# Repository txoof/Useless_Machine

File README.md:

# Useless Machine

## *Absolutely Useless, Completely Necessary*

This useless machine comes with everything you need to laser cut and assemble a box and add hardware of your choice. Both designs physically disconnect the batteries when not in use to provide months and months of useless uselessness!

It even comes in two flavors:
## [ItsyBitsy Version](ItsyBitsy_Version/ItsyBitsy_README.md)

The ItsyBitsy version is sassy, slightly passive aggressive, has lights, is programmable and hackable! It runs on AdaFruit's Circuit Python and code is well documented and easily modified with options for adding additional attack/retreat modes.

There's even a PCB schematic you can spin out from OSH Park or one of the other fab houses.
## [555 Timer Version ](555_Version/555_README.md)

This version is a fun way to explore PWM and 555 timers. The venerable 555 is a great tool for making das blinken lights, but also for driving pulse-width-modulated hardware like servos.

The 555 Version requires just a few parts and can be fabricated at home with protoboard or etching your own circuit. There are resist masks, drill instructions, a BOM and everything you need to build a your own 555 Useless Machine.

## [The Box](./enclosure/Enclosure_README.md)

Fire up the pew-pew laser and make yourself a box! Everything you need to create your own laser-cut box is here including DXF, SVG, artwork and OpenSCAD files. The DXF and SVG versions are set up for 4mm birch ply. If you intend to use something thicker or thinner, make sure you generate a new layout using the OpenSCAD files.

The OpenSCAD version is customizable takes advantage of the OpenSCAD customizer interface. M

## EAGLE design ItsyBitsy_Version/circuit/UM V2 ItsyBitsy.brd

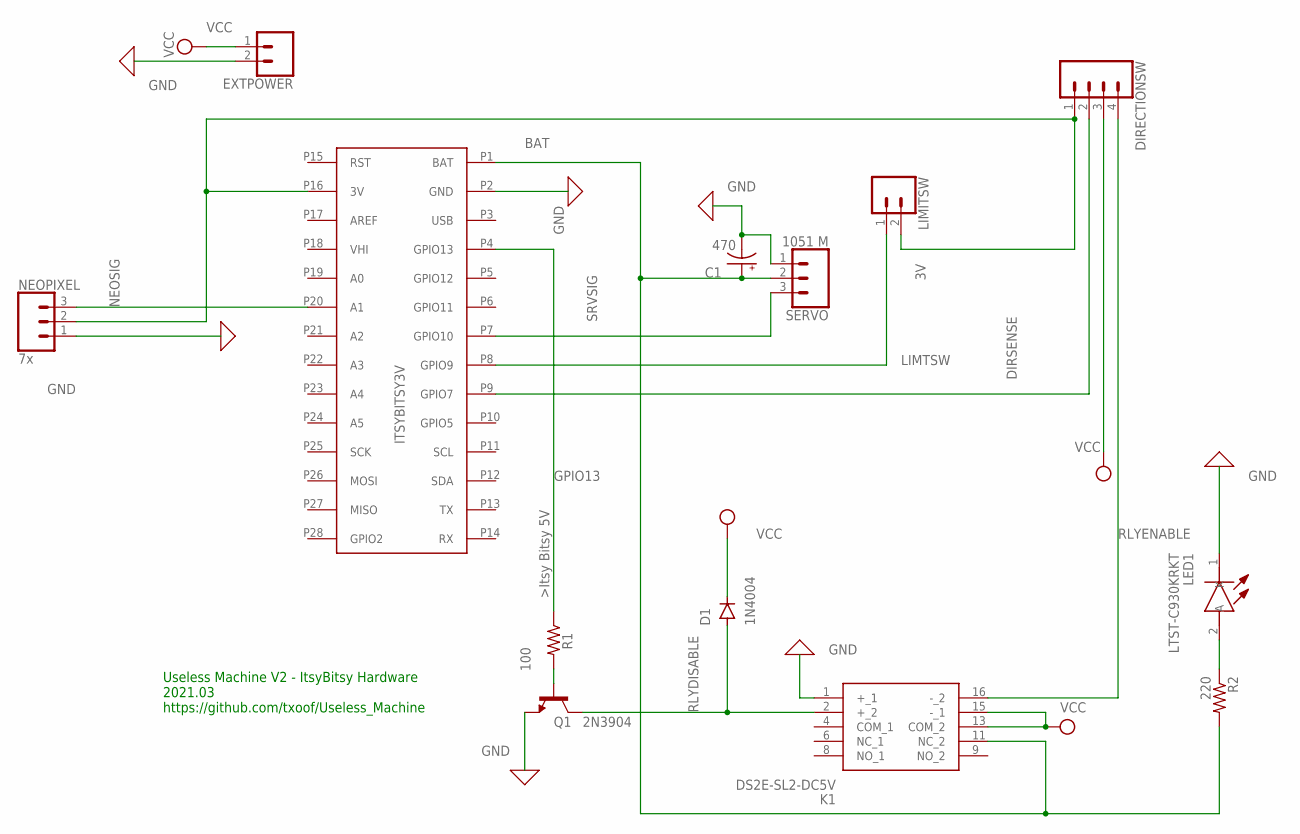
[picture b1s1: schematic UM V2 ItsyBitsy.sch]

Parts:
C1: 470; E2,5-6E
D1: 1N4004; DO41-10
DIRECTIONSW: Direction Sw; MOLEX-1X4
EXTPOWER: Limit Sw; MOLEX-1X2
K1: DS2E-SL2-DC5V; DS2ESL2DC5V
LED1: LTST-C930KRKT; LTSTC930KRKT
LIMITSW: Limit Sw; MOLEX-1X2
NEOPIXEL: 7x; MOLEX-1X3
Q1: 2N3904; TO92-CBE
R1: 100; M1206
R2: 220; M1206
SERVO: 1051 M; MOLEX-1X3
U$1: ITSYBITSY3V

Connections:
3V: DIRECTIONSW.1, LIMITSW.2, NEOPIXEL.2, U$1.P16 (3V)
BAT: C1.+, K1.11 (NC_2), R2.2, SERVO.2, U$1.P1 (BAT)
DIRSENSE: DIRECTIONSW.2, U$1.P9 (GPIO7)
GND: C1.-, EXTPOWER.2, K1.1 (+_1), LED1.1 (K), NEOPIXEL.1, Q1.E, SERVO.1, U$1.P2 (GND)
GPIO13: R1.1, U$1.P4 (GPIO13)
LIMTSW: LIMITSW.1, U$1.P8 (GPIO9)
unnamed: LED1.2 (A), R2.1
unnamed: Q1.B, R1.2
NEOSIG: NEOPIXEL.3, U$1.P20 (A1)
RLYDISABLE: D1.A, K1.2 (+_2), Q1.C
RLYENABLE: DIRECTIONSW.4, K1.16 (-_2)
SRVSIG: SERVO.3, U$1.P7 (GPIO10)
VCC: D1.C, DIRECTIONSW.3, EXTPOWER.1, K1.13 (COM_2), K1.15 (-_1)

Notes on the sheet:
Useless Machine V2 - ItsyBitsy Hardware 2021.03 https://github.com/txoof/Useless_Machine

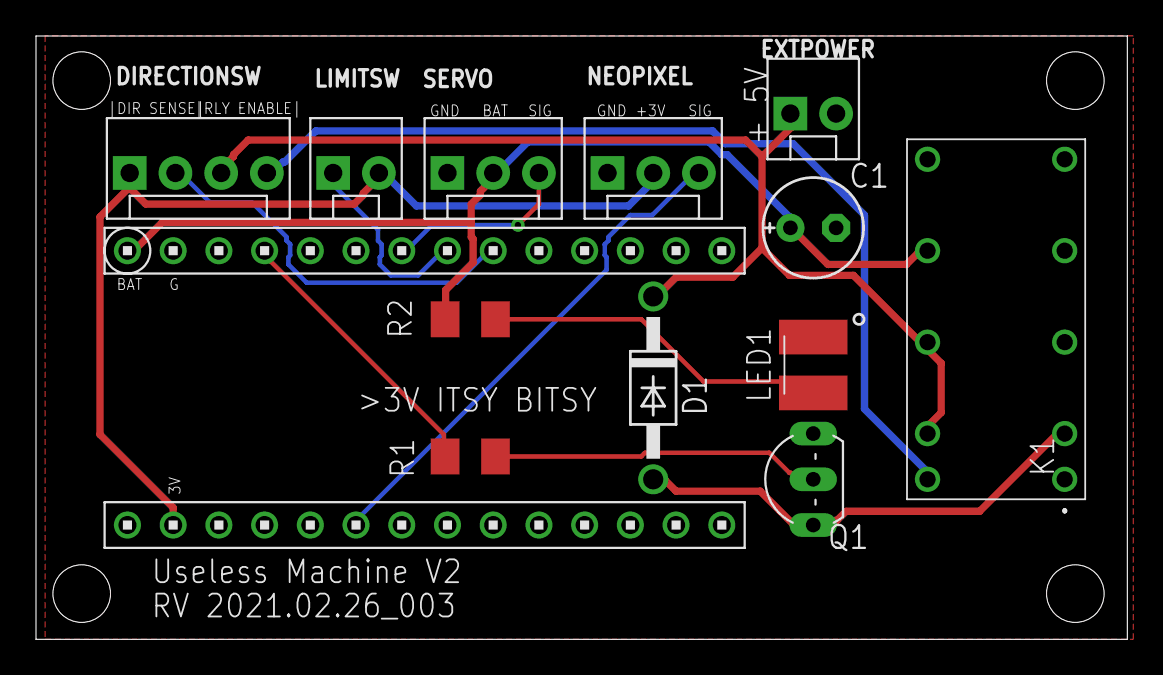
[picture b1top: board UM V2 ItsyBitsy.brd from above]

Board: 2 copper layers, 60.6 x 33.5 mm, 13 parts (0 on the bottom side), 13 nets.

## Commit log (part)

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2021-01-30 atom auto copy
2021-01-30 update goals
2021-01-30 improve pause
2021-02-06 update Notes
2021-02-07 add colors, simplify code
2021-03-20 update libraries
2022-12-04 Reorganization of repo and addition of readmes

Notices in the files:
parts and their libraries:
SparkFun-Connectors: Licensing: Creative Commons ShareAlike 4.0 International - https://creativecommons.org/licenses/by-sa/4.0
